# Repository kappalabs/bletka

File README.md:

BLETKA
======
Bluetooth Low Energy Time Keeper supporting Android
---------------------------------------------------

BLETKA is device, which should provide only single button
and no other inputs. When you push this button, BLETKA will
make a sound or light effect and will save internally a record
containing current time and date.
When the button is pushed for longer time, BLETKA will
turn on its BLE module and it will provide set of commands,
which can be used to manage records and even configure
the device itself.

BLETKA was designed, created and tested on ATMEGA 328P-PU microcontroller
using HM-10 BLE module and RTC module DS1307 with 5 buttons
(instead of just single one).

The project is divided into two main parts:
  1. written in AVR assembly code
   - low level library providing interface for simple communication with all peripherals
  2. written in C code
   - program implementing the project using the assembly library
   
BLETKA circuit diagrams:
------------------------
* BLETKA with 5 buttons

* BLETKA with 1 button

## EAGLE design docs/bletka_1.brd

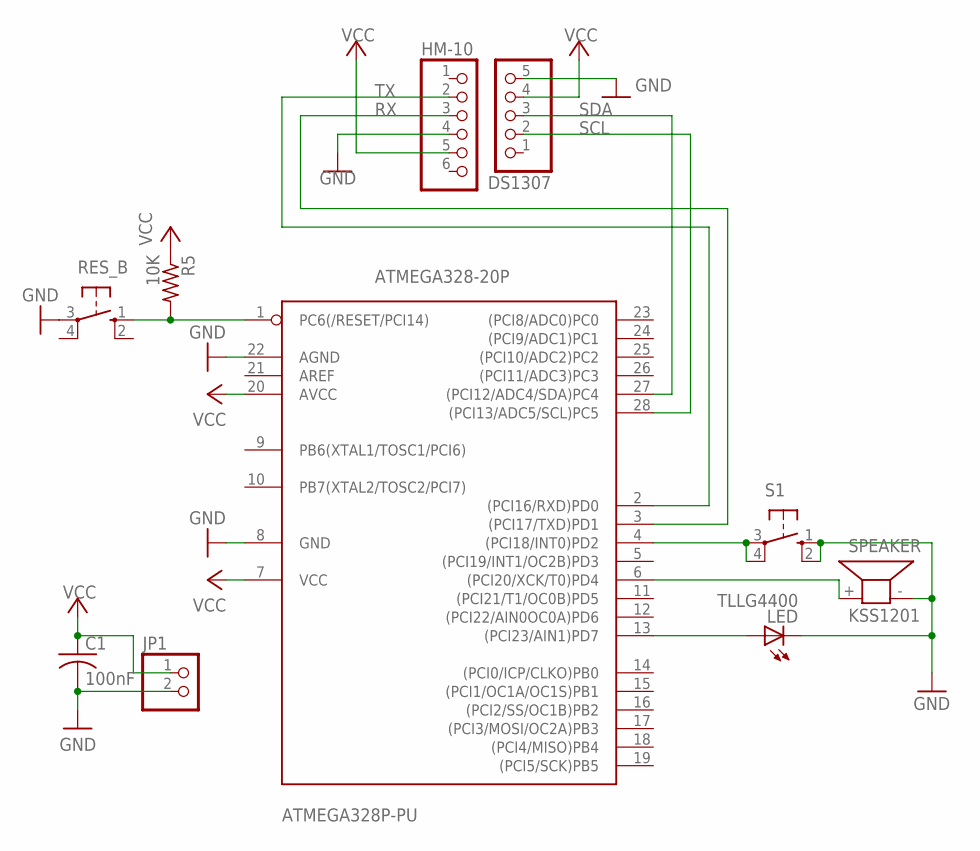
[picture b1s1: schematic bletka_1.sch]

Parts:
ATMEGA328P-PU: ATMEGA328-20P; DIL28-3
C1: 100nF; C050-024X044
DS1307: PINHD-1X5; 1X05
HM-10: PINHD-1X6; 1X06
JP1: PINHD-1X2; 1X02
LED: TLLG4400; LED3MM
R5: 10K; 0207/10
RES_B: 10-XX; B3F-10XX
S1: 10-XX; B3F-10XX
SPEAKER: KSS1201

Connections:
GND: ATMEGA328P-PU.8 (GND), ATMEGA328P-PU.22 (AGND), C1.2, DS1307.5, HM-10.4, JP1.2, LED.K (C), RES_B.3, S1.1 (S), S1.2 (S1), SPEAKER.- (2)
unnamed: ATMEGA328P-PU.4 ((PCI18/INT0)PD2), S1.3, S1.4 (P1)
PD4: ATMEGA328P-PU.6 ((PCI20/XCK/T0)PD4), SPEAKER.+ (1)
PD7: ATMEGA328P-PU.13 ((PCI23/AIN1)PD7), LED.A
RESET: ATMEGA328P-PU.1 (PC6(/RESET/PCI14)), R5.2, RES_B.1 (S)
RX: ATMEGA328P-PU.3 ((PCI17/TXD)PD1), HM-10.3
SCL: ATMEGA328P-PU.28 ((PCI13/ADC5/SCL)PC5), DS1307.2
SDA: ATMEGA328P-PU.27 ((PCI12/ADC4/SDA)PC4), DS1307.3
TX: ATMEGA328P-PU.2 ((PCI16/RXD)PD0), HM-10.2
VCC: ATMEGA328P-PU.7 (VCC), ATMEGA328P-PU.20 (AVCC), C1.1, DS1307.4, HM-10.5, JP1.1, R5.1

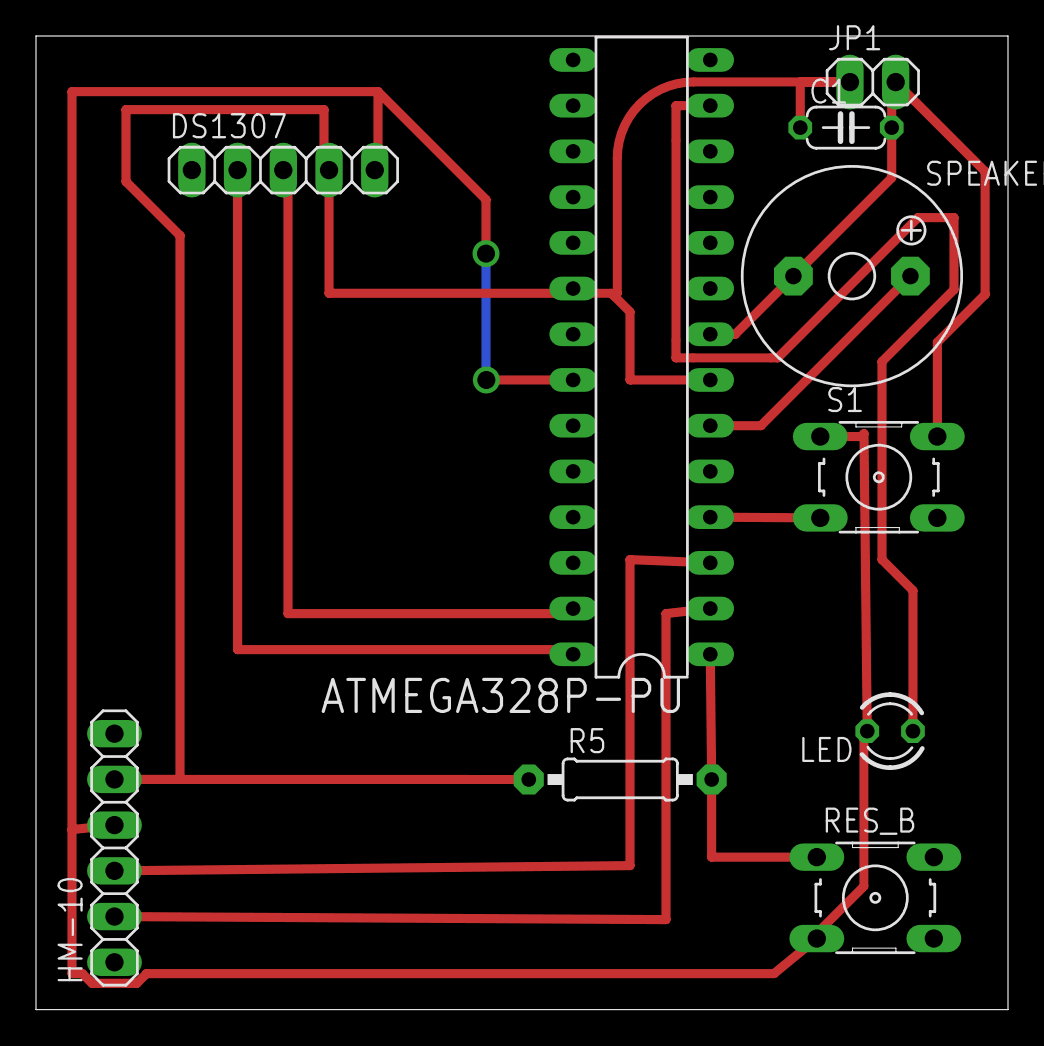
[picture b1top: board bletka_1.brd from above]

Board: 2 copper layers, 54.0 x 54.1 mm, 10 parts (0 on the bottom side), 10 nets.

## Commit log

2017-03-25 [TASK] Initial commit
    - RTC & BLE module communication works as it should
    - interrupts from buttons are handled
    - LED & speaker can signal states as desired
    - TWI communication could possibly be implemented using interrupts in future
    - only few commands are needed to be completed
2017-03-25 [TASK] Added README.md
    - added basic description of this project
2017-04-09 [WIP|FEATURE] RECMEM operations
    - adds 10ms and 20ms assembler delays
    - fixes RECROM write not waiting for delay specified in documentation
    - ble_receive/transmit supports boolean to specify if strictly 'N' characters should be processed
    - BLE initialization now supports response confirmations
    - RJMP in interrupts changed to JMP due to expansion of the program code size
    - adds support for new command to purge whole RECMEM
2017-04-11 [FEATURE|CLEANUP] BLE receiving
    - changes the way receive from BLE module is done - buffer is now used
    allowing parallel transmission & receive
    - new approach is less power-efficient but necessary to receive all
    BLE responses to commands
    - adds new command to print content of the RECMEM
    - adds 'volatile' keyword to variables accessed by assembly code
2017-04-12 [BUGFIX] RECROM Pages
    - fixes write to RECROM, which is now done with respect to EEPROM pages
    - fixes volatile _timeram_buff warnings with castings
2017-04-13 [BUGFIX] RECMEM Utilities Inspection
    - fixes procedure of record's destruction in RECROM
    - fixes RECROM rotation procedure
    - handles full memory with sound effects
    - adds documentation to all RECMEM utilities
    - removes unnecessary debug messages
    - changes EEPROM write delay to support less voltage level (now from 1.8V
2017-04-15 [CLEANUP] Fancy Comments
    - changes comments in utils.S missing some properties of used documentation style
    - changes compress_time: to use less variables/registers
2017-04-16 [BUGFIX] Bugs Born from Documentation
    - fixes strict mode not working properly for ble_nreceive() function
    - changes name of weird_to_binary() which appears to be a standard named BCD
    - fixes that incorrect command without number parameter could cause problems in RECMEM
2017-04-16 [TASK] PDF Document
    - adds documentation for this project
2017-04-19 [BUGFIX] More Bugs
    - fixes reading of parameters in ble_nreceive()
    - fixes compression not working due to r0 usage in bcd_to_binary by changing it back as it was
    - adds more delay before going to BLE sleep and after connection is established for safety
2017-05-15 [FEATURE] Schematic Diagram
    - adds circuit diagram for BLETKA with 5 buttons
2017-05-16 [FEATURE] Schematic Diagram
    - adds image to readme circuit diagram for BLETKA with 5 buttons
2017-05-16 [FEATURE] Schematic Diagram & Board
    - adds images of BLETKA with 1 button to readme
